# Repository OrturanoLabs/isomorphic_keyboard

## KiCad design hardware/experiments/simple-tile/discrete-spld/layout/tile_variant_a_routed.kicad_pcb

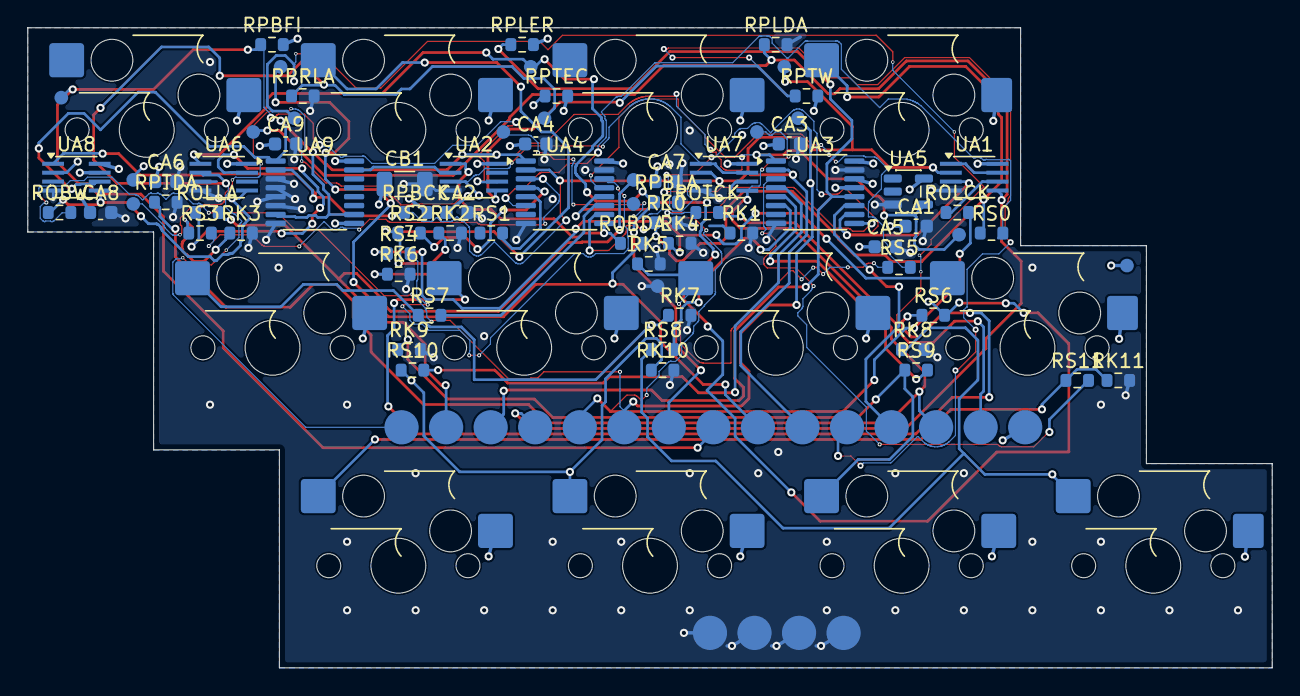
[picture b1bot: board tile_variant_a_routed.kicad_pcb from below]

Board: 4 copper layers, 90.8 x 46.7 mm, 105 parts (93 on the bottom side), 52 nets.

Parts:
CA1: 100n; CA1
CA2: 100n; CA2
CA3: 100n; CA3
CA4: 100n; CA4
CA5: 100n; CA5
CA6: 100n; CA6
CA7: 100n; CA7
CA8: 100n; CA8
CA9: 100n; CA9
CB1: 4u7; CB1
JP_B_W: PAD2.5; JP_B_W
JP_B_clk: PAD2.5; JP_B_clk
JP_B_data: PAD2.5; JP_B_data
JP_B_first: PAD2.5; JP_B_first
JP_B_latch: PAD2.5; JP_B_latch
JP_GND: PAD2.5; JP_GND
JP_GND_DET_B: PAD2.5; JP_GND_DET_B
JP_GND_DET_R: PAD2.5; JP_GND_DET_R
JP_GND_DET_T: PAD2.5; JP_GND_DET_T
JP_L_clk: PAD2.5; JP_L_clk
JP_L_data: PAD2.5; JP_L_data
JP_L_endrow: PAD2.5; JP_L_endrow
JP_L_latch: PAD2.5; JP_L_latch
JP_R_latch: PAD2.5; JP_R_latch
JP_T_W: PAD2.5; JP_T_W
JP_T_clk: PAD2.5; JP_T_clk
JP_T_data: PAD2.5; JP_T_data
JP_T_endcol: PAD2.5; JP_T_endcol
JP_VCC: PAD2.5; JP_VCC
RK0: 10k; RK0
RK1: 10k; RK1
RK2: 10k; RK2
RK3: 10k; RK3
RK4: 10k; RK4
RK5: 10k; RK5
RK6: 10k; RK6
RK7: 10k; RK7
RK8: 10k; RK8
RK9: 10k; RK9
RK10: 10k; RK10
RK11: 10k; RK11
ROBDA: 33; ROBDA
ROBW: 33; ROBW
ROLCK: 33; ROLCK
ROLLA: 33; ROLLA
ROTCK: 33; ROTCK
RPBCK: 10k; RPBCK
RPBFI: 10k; RPBFI
RPBLA: 10k; RPBLA
RPLDA: 10k; RPLDA
RPLER: 10k; RPLER
RPRLA: 10k; RPRLA
RPTDA: 10k; RPTDA
RPTEC: 10k; RPTEC
RPTW: 10k; RPTW
RS0: 100; RS0
RS1: 100; RS1
RS2: 100; RS2
RS3: 100; RS3
RS4: 100; RS4
RS5: 100; RS5
RS6: 100; RS6
RS7: 100; RS7
RS8: 100; RS8
RS9: 100; RS9
RS10: 100; RS10
RS11: 100; RS11
SW1: SW; SW1
SW2: SW; SW2
SW3: SW; SW3
SW4: SW; SW4
SW5: SW; SW5
SW6: SW; SW6
SW7: SW; SW7
SW8: SW; SW8
SW9: SW; SW9
SW10: SW; SW10
SW11: SW; SW11
SW12: SW; SW12
TP_B_W: B_W; TP_B_W
TP_B_clk: B_clk; TP_B_clk
TP_B_data: B_data; TP_B_data
TP_B_first: B_first; TP_B_first
TP_B_latch: B_latch; TP_B_latch
TP_GND: GND; TP_GND
TP_L_clk: L_clk; TP_L_clk
TP_L_data: L_data; TP_L_data
TP_L_latch: L_latch; TP_L_latch
TP_R_latch: R_latch; TP_R_latch
TP_T_clk: T_clk; TP_T_clk
TP_T_data: T_data; TP_T_data
TP_VCC: VCC; TP_VCC
TP_W: W; TP_W
TP_data_drv: data_drv; TP_data_drv
TP_latch_drv: latch_drv; TP_latch_drv
TP_nRST: nRST; TP_nRST
UA1: SN74LVC2G126; UA1
UA2: SN74LVC2G08; UA2
UA3: SN74LVC165A; UA3
UA4: SN74LVC165A; UA4
UA5: SN74LVC1G04; UA5
UA6: SN74LVC2G32; UA6
UA7: SN74LVC2G125; UA7
UA8: SN74LVC2G74; UA8
UA9: SN74LV161A; UA9

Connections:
B_W: JP_B_W.1, ROBW.2, TP_B_W.1
B_W_drv: ROBW.1, UA6.5, UA8.5
B_clk: JP_B_clk.1, RPBCK.1, TP_B_clk.1, UA1.2, UA3.2, UA4.2, UA7.2, UA8.1, UA9.2
B_data: JP_B_data.1, ROBDA.2, TP_B_data.1
B_first: JP_B_first.1, RPBFI.1, TP_B_first.1, UA2.6
B_latch: JP_B_latch.1, RPBLA.1, TP_B_latch.1, UA6.1
CHAIN: UA3.9, UA4.10
DS_net: UA1.3, UA3.10, UA7.3
GND: CA1.2, CA2.2, CA3.2, CA4.2, CA5.2, CA6.2, CA7.2, CA8.2, CA9.2, CB1.2, JP_GND.1, JP_GND_DET_B.1, JP_GND_DET_R.1, JP_GND_DET_T.1, RK0.2, RK1.2, RK2.2, RK3.2, RK4.2, RK5.2, RK6.2, RK7.2, RK8.2, RK9.2, RK10.2, RK11.2, RPBLA.2, RPLDA.2, RPRLA.2, RPTDA.2, TP_GND.1, UA1.4, UA2.4, UA3.8, UA3.15, UA4.8, UA4.15, UA5.3, UA6.4, UA7.4, UA8.4, UA9.3, UA9.4, UA9.5, UA9.6, UA9.8
KEY0: RS0.2, UA4.6
KEY1: RS1.2, UA4.5
KEY2: RS2.2, UA4.4
KEY3: RS3.2, UA4.3
KEY4: RS4.2, UA4.14
KEY5: RS5.2, UA4.13
KEY6: RS6.2, UA4.12
KEY7: RS7.2, UA4.11
KEY8: RS8.2, UA3.6
KEY9: RS9.2, UA3.5
KEY10: RS10.2, UA3.4
KEY11: RS11.2, UA3.3
L_clk: JP_L_clk.1, ROLCK.2, TP_L_clk.1
L_clk_drv: ROLCK.1, UA1.6
L_data: JP_L_data.1, RPLDA.1, TP_L_data.1, UA1.5
L_endrow: JP_L_endrow.1, RPLER.1, UA3.12
L_latch: JP_L_latch.1, ROLLA.2, TP_L_latch.1
R_latch: JP_R_latch.1, RPRLA.1, TP_R_latch.1, UA6.2
SWN0: RK0.1, RS0.1, SW1.2
SWN1: RK1.1, RS1.1, SW2.2
SWN2: RK2.1, RS2.1, SW3.2
SWN3: RK3.1, RS3.1, SW4.2
SWN4: RK4.1, RS4.1, SW5.2
SWN5: RK5.1, RS5.1, SW6.2
SWN6: RK6.1, RS6.1, SW7.2
SWN7: RK7.1, RS7.1, SW8.2
SWN8: RK8.1, RS8.1, SW9.2
SWN9: RK9.1, RS9.1, SW10.2
SWN10: RK10.1, RS10.1, SW11.2
SWN11: RK11.1, RS11.1, SW12.2
T_W: JP_T_W.1, RPTW.1, UA2.5
T_clk: JP_T_clk.1, ROTCK.2, TP_T_clk.1
T_clk_drv: ROTCK.1, UA7.6
T_data: JP_T_data.1, RPTDA.1, TP_T_data.1, UA7.5
T_endcol: JP_T_endcol.1, RPTEC.1, UA3.11
Tc: UA2.2, UA9.15
VCC: CA1.1, CA2.1, CA3.1, CA4.1, CA5.1, CA6.1, CA7.1, CA8.1, CA9.1, CB1.1, JP_VCC.1, RPBCK.2, RPBFI.2, RPLER.2, RPTEC.2, RPTW.2, SW1.1, SW2.1, SW3.1, SW4.1, SW5.1, SW6.1, SW7.1, SW8.1, SW9.1, SW10.1, SW11.1, SW12.1, TP_VCC.1, UA1.8, UA2.8, UA3.13, UA3.14, UA3.16, UA4.16, UA5.5, UA6.8, UA7.8, UA8.7, UA8.8, UA9.9, UA9.16
W: TP_W.1, UA1.1, UA1.7, UA2.3, UA7.1, UA7.7
data_drv: ROBDA.1, TP_data_drv.1, UA2.1, UA4.9
flag_and: UA2.7, UA6.6
flag_d: UA6.3, UA8.2
latch_drv: ROLLA.1, TP_latch_drv.1, UA5.2, UA6.7
nRST: TP_nRST.1, UA3.1, UA4.1, UA5.4, UA8.6, UA9.1, UA9.7, UA9.10
